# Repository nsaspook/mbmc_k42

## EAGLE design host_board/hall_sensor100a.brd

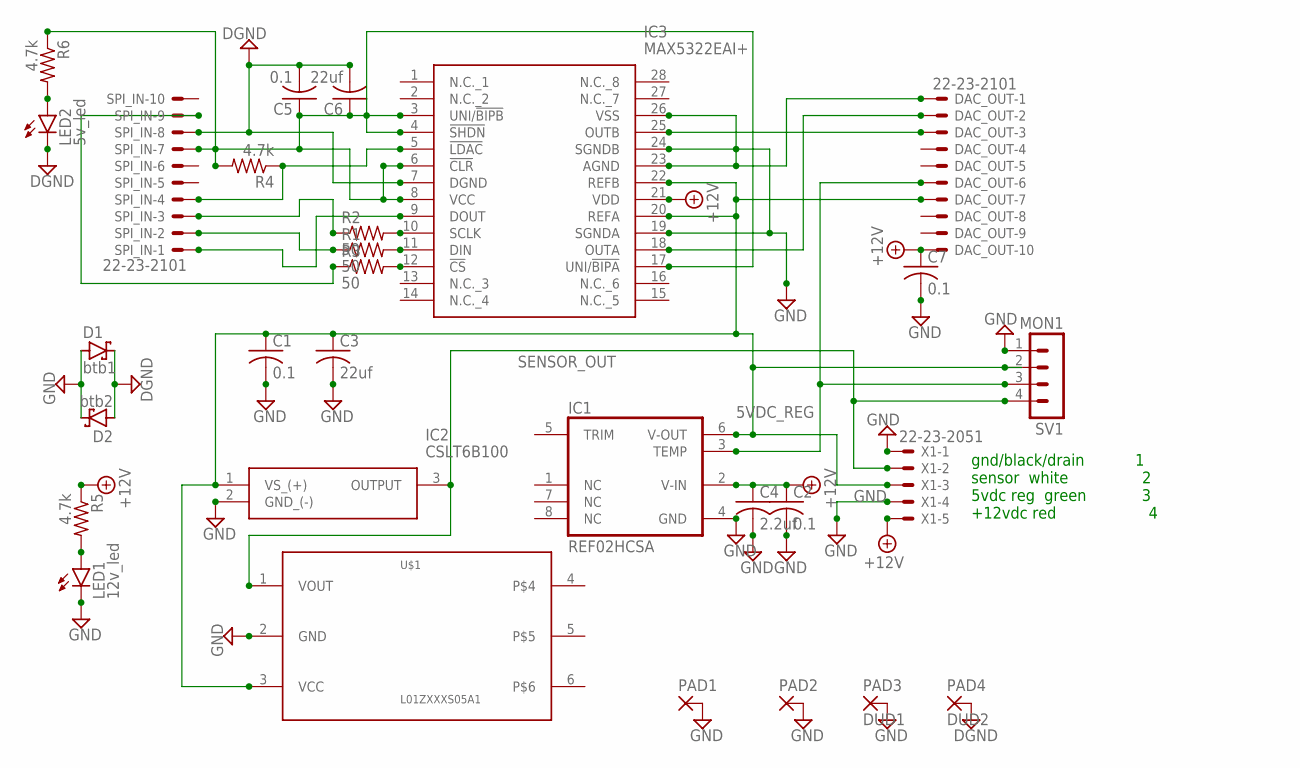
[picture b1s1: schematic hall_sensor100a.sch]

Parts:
C1, C2, C5, C7: 0.1; C0805
C3, C6: 22uf; C0805
C4: 2.2uf; C0805
D1: btb1; DO35-7
D2: btb2; DO35-7
DAC_OUT: 22-23-2101
IC1: REF02HCSA; SO08
IC2: CSLT6B100
IC3: MAX5322EAI+; SOP65P778X199-28N
LED1: 12v_led; CHIPLED_1206
LED2: 5v_led; CHIPLED_1206
PAD1, PAD2: 2,15/1,0
PAD3: DUD1; 2,15/1,0
PAD4: DUD2; 2,15/1,0
R1, R2, R3: 50; M0805
R4, R5, R6: 4.7k; M0805
SPI_IN: 22-23-2101
SV1: MON1; MA04-1
U$1: L01ZXXXS05A1; DIP2540W53P254L2900H508Q6B
X1: 22-23-2051

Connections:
5VDC_REG: C1.1, C3.1, DAC_OUT.7, IC1.6 (V-OUT), IC2.1 (VS_(+)), IC3.20 (REFA), IC3.22 (REFB), SV1.2, U$1.3 (VCC), X1.3
+12V: C2.1, C4.1, C7.1, DAC_OUT.10, IC1.2 (V-IN), IC3.21 (VDD), R5.1, X1.5
DGND: C5.2, C6.2, D1.C, D2.A, IC3.7 (DGND), LED2.C, PAD4.1, SPI_IN.8
GND: C1.2, C2.2, C3.2, C4.2, C7.2, D1.A, D2.C, DAC_OUT.1, IC1.4 (GND), IC2.2 (GND_(-)), IC3.19 (SGNDA), IC3.23 (AGND), IC3.24 (SGNDB), IC3.26 (VSS), LED1.C, PAD1.1, PAD2.1, PAD3.1, SV1.1, U$1.2 (GND), X1.1, X1.4
unnamed: IC3.11 (DIN), R1.2
unnamed: DAC_OUT.2, IC3.18 (OUTA)
unnamed: DAC_OUT.3, IC3.25 (OUTB)
unnamed: R1.1, SPI_IN.2
unnamed: IC3.9 (DOUT), SPI_IN.1
unnamed: R2.1, SPI_IN.3
unnamed: R3.1, SPI_IN.9
unnamed: C5.1, C6.1, IC3.3 (UNI/!BIPB), IC3.4 (!SHDN), IC3.6 (!CLR), IC3.8 (VCC), IC3.17 (UNI/!BIPA), R4.2, R6.1, SPI_IN.7
unnamed: LED1.A, R5.2
unnamed: IC3.5 (!LDAC), R4.1, SPI_IN.4
unnamed: IC3.10 (SCLK), R2.2
unnamed: IC3.12 (!CS), R3.2
unnamed: DAC_OUT.6, IC1.3 (TEMP), SV1.3
unnamed: LED2.A, R6.2
SENSOR_OUT: IC2.3 (OUTPUT), SV1.4, U$1.1 (VOUT), X1.2

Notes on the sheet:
gnd/black/drain 1 sensor white 2 5vdc reg green 3 +12vdc red 4

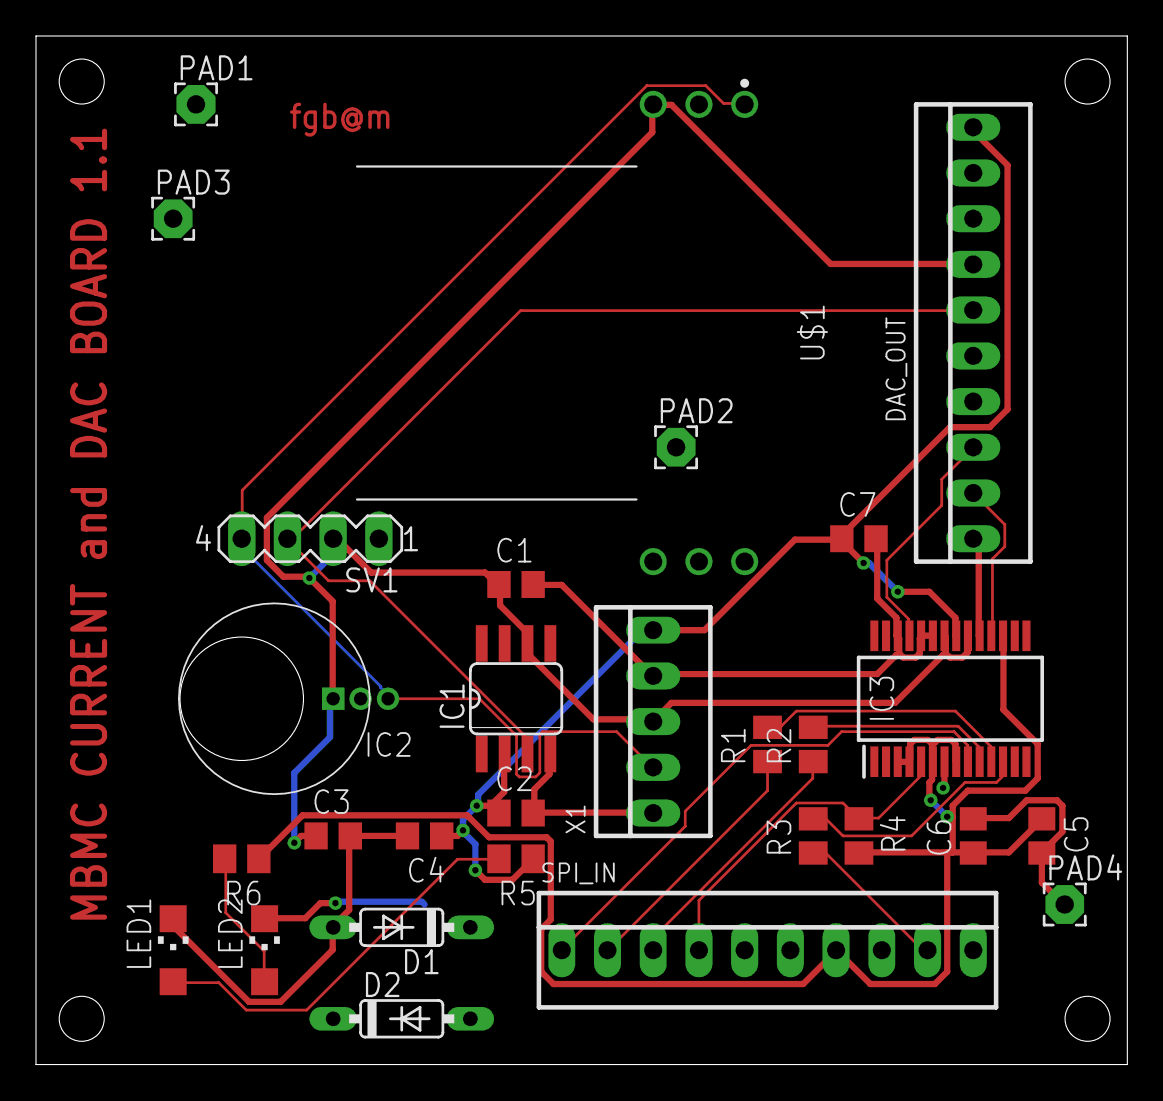
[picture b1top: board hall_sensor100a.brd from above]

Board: 2 copper layers, 60.6 x 57.1 mm, 29 parts (0 on the bottom side), 19 nets.

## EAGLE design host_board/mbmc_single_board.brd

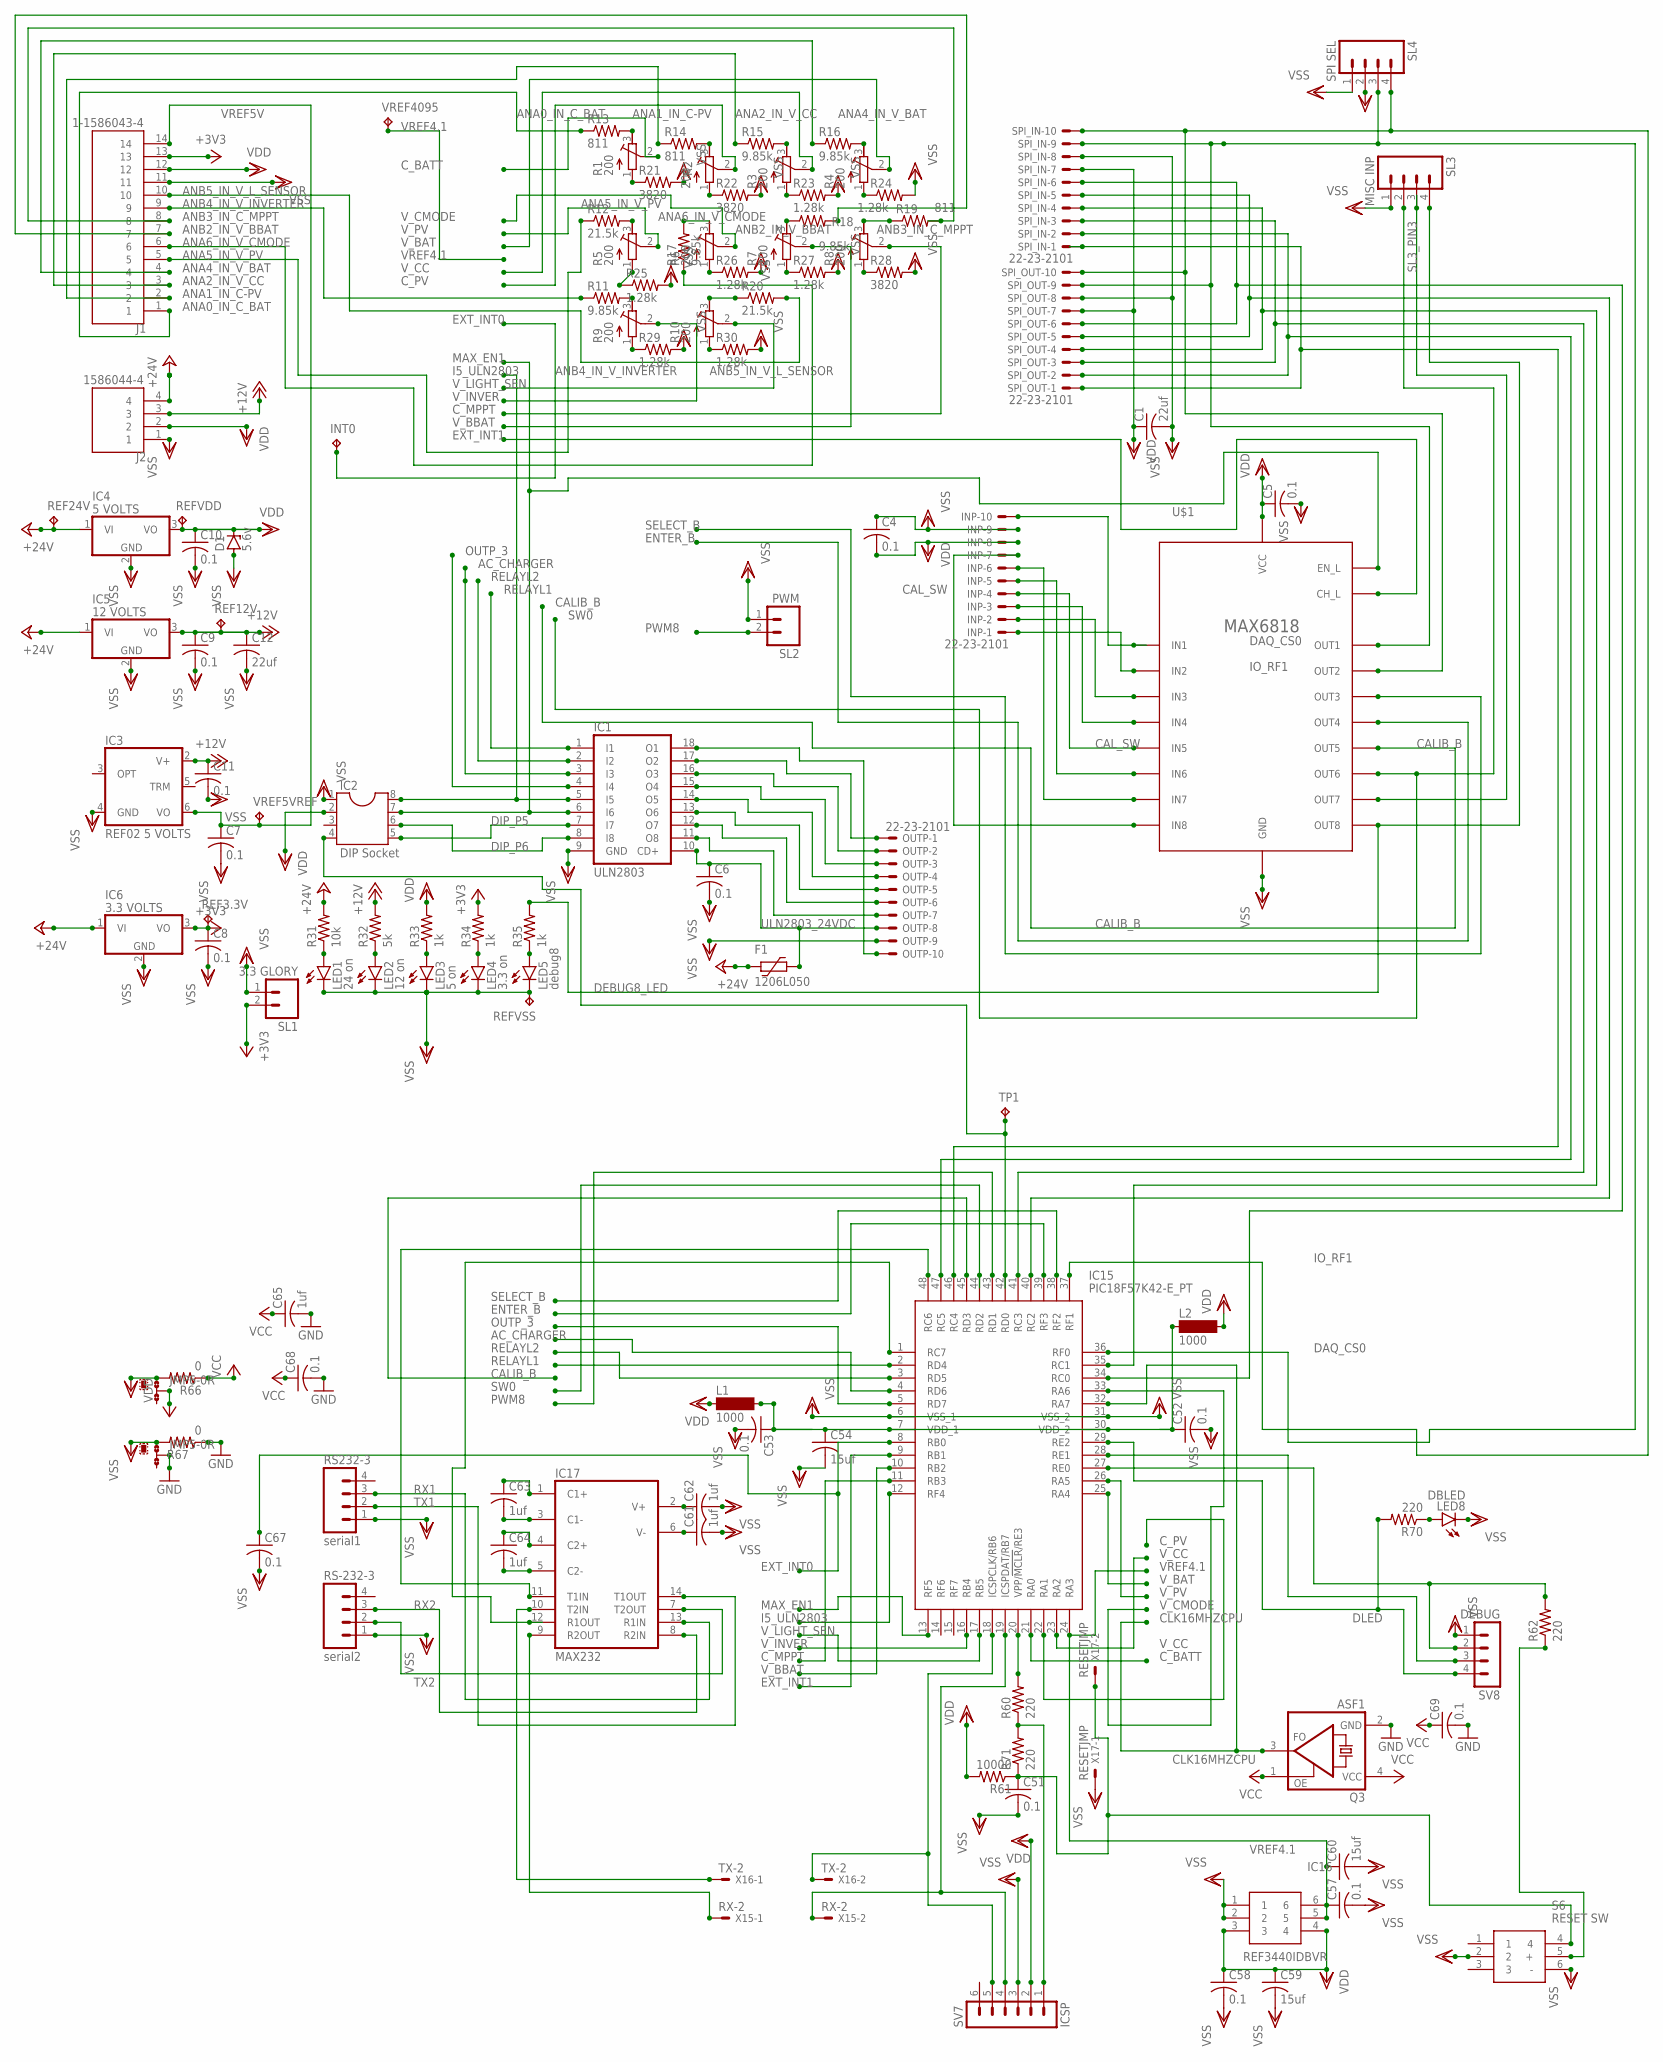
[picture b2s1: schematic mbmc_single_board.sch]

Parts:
C1, C12: 22uf; C0805
C4, C5, C6, C7, C8, C9, C10, C11: 0.1; C0805
C51, C52, C53, C57, C58, C67, C68, C69: 0.1; C1206
C54, C59, C60: 15uf; C1206
C61, C62, C63, C64, C65: 1uf; C0805
D1: 5.6v; ZDIO-2.5
F1: 1206L050; 1206L
IC1: ULN2803; DIL18
IC2: DIP Socket; SOCKET-08
IC3: REF02 5 VOLTS; DIL08
IC4: 5 VOLTS; TO220V
IC5: 12 VOLTS; TO220V
IC6: 3.3 VOLTS; TO220V
IC15: PIC18F57K42-E_PT; QFP50P900X900X120-48N
IC16: REF3440IDBVR; SOP95P280X145-6N
IC17: MAX232; DIL16
INP: 22-23-2101
INT0: TPB1,27; B1,27
J1: 1-1586043-4; TE_1-1586043-4
J2: 1586044-4; TE_1586044-4
JMP5, JMP6: 0R-JUMPA; A0R-JMP
L1, L2: 1000; SM-1206
LED1: 24 on; CHIPLED_1206
LED2: 12 on; CHIPLED_1206
LED3: 5 on; CHIPLED_1206
LED4: 3.3 on; CHIPLED_1206
LED5: debug8; CHIPLED_1206
LED8: DBLED; CHIPLED_1206
OUTP: 22-23-2101
Q3: ASF1; ASF
R1, R2, R3, R4, R5, R6, R7, R8, R9, R10: 200; RTRIM3339P
R11, R15, R16, R17, R18: 9.85k; R0805
R12, R20: 21.5k; R0805
R13, R14, R19: 811; R0805
R21, R22, R28: 3820; R0805
R23, R24, R25, R26, R27, R29, R30: 1.28k; R0805
R31: 10k; R0805
R32: 5k; R0805
R33, R34, R35: 1k; R0805
R60, R62, R70, R71: 220; R1206
R61: 10000; R1206
R66, R67: 0; R1206
REF3.3V, REF12V, REF24V: TPB1,27; B1,27
REFVDD: TPB1,27; B1,27
REFVSS: TPB1,27; B1,27
RS232-3: serial1; 04P
RS-232-3: serial2; 04P
S6: RESET SW; B3W-9_1-LED
SL1: 3.3 GLORY; 02P
SL2: PWM; 02P
SL3: MISC INP; 04P
SL4: SPI SEL; 04P
SPI_IN: 22-23-2101
SPI_OUT: 22-23-2101
SV7: ICSP; MA06-1
SV8: DEBUG; MA04-1
TP1: TPB1,27; B1,27
U$1: MAX6818; SSOP20
VREF5VREF, VREF4095: TPB1,27; B1,27
X15: RX-2; 332-02
X16: TX-2; 332-02
X17: RESETJMP; 332-02

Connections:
+3V3: C8.1, IC6.3 (VO), J1.13, R34.2, REF3.3V.TP, SL1.2
+12V: C9.1, C11.1, C12.1, IC3.2 (V+), IC5.3 (VO), J2.3, R32.2, REF12V.TP
+24V: F1.2, IC4.1 (VI), IC5.1 (VI), IC6.1 (VI), J2.4, R31.2, REF24V.TP
AC_CHARGER: IC1.3 (I3), IC15.4 (RD6)
ANA0_IN_C_BAT: J1.1, R13.1
ANA1_IN_C-PV: J1.2, R14.1
ANA2_IN_V_CC: J1.3, R15.1
ANA4_IN_V_BAT: J1.4, R16.1
ANA5_IN_V_PV: J1.5, R12.1
ANA6_IN_V_CMODE: J1.6, R17.1
ANB2_IN_V_BBAT: J1.7, R18.2
ANB3_IN_C_MPPT: J1.8, R19.2
ANB4_IN_V_INVERTER: J1.9, R11.1
ANB5_IN_V_L_SENSOR: J1.10, R20.2
CALIB_B: IC15.45 (RD3), U$1.OUT5
CAL_SW: INP.4, U$1.IN5
CLK16MHZCPU: IC15.32 (RA7), Q3.3 (FO)
C_BATT: IC15.21 (RA0), R1.2 (S)
C_MPPT: IC15.11 (RB3), R8.2 (S)
C_PV: IC15.22 (RA1), R2.2 (S)
DAQ_CS0: IC15.36 (RF0), SL4.3, SPI_IN.9, SPI_OUT.9, U$1.OUT1
DEBUG8_LED: R35.2, SL3.4, U$1.OUT8
DIP_P5: IC1.7 (I7), IC2.5
DIP_P6: IC1.8 (I8), IC2.6
DLED: IC15.29 (RE2), R70.2, SV8.4
ENTER_B: IC15.39 (RF3), U$1.OUT4
EXT_INT0: C67.1, IC15.8 (RB0), INT0.TP
EXT_INT1: IC15.9 (RB1), U$1.CH_L
GND: C65.2, C68.2, C69.2, IC17.15 (GND), JMP5.2, Q3.2 (GND), R67.1
I5_ULN2803: IC1.5 (I5), IC2.8, IC15.12 (RF4)
IO_RF1: IC15.37 (RF1), SL4.4, SPI_IN.10, SPI_OUT.10, U$1.OUT2
MAX_EN1: IC1.6 (I6), IC2.7, IC15.13 (RF5), U$1.EN_L
unnamed: R9.3 (E), R11.2
unnamed: R5.3 (E), R12.2
unnamed: R1.3 (E), R13.2
unnamed: R2.3 (E), R14.2
unnamed: R3.3 (E), R15.2
unnamed: R4.3 (E), R16.2
unnamed: R6.3 (E), R17.2
unnamed: R8.3 (E), R19.1
unnamed: R1.1 (A), R21.1
unnamed: R2.1 (A), R22.1
unnamed: R3.1 (A), R23.1
unnamed: R4.1 (A), R24.1
unnamed: R5.1 (A), R25.1
unnamed: R6.1 (A), R26.1
unnamed: R7.1 (A), R27.1
unnamed: R8.1 (A), R28.1
unnamed: R9.1 (A), R29.1
unnamed: R10.1 (A), R30.1
unnamed: C52.1, C53.1, C54.1, IC15.7 (VDD_1), IC15.30 (VDD_2), L1.2, L2.1
unnamed: INP.10, U$1.IN1
unnamed: INP.1, U$1.IN2
unnamed: INP.2, U$1.IN3
unnamed: INP.3, U$1.IN4
unnamed: INP.5, U$1.IN6
unnamed: INP.6, U$1.IN7
unnamed: INP.7, U$1.IN8
unnamed: IC1.18 (O1), OUTP.10
unnamed: IC1.17 (O2), OUTP.1
unnamed: IC1.16 (O3), OUTP.2
unnamed: IC1.15 (O4), OUTP.3
unnamed: IC1.14 (O5), OUTP.4
unnamed: IC1.13 (O6), OUTP.5
unnamed: IC1.12 (O7), OUTP.6
unnamed: IC1.11 (O8), OUTP.7
unnamed: IC15.46 (RC4), SPI_IN.1, SPI_OUT.1
unnamed: LED1.A, R31.1
unnamed: LED2.A, R32.1
unnamed: LED3.A, R33.1
unnamed: LED4.A, R34.1
unnamed: LED5.A, R35.1
unnamed: R10.3 (E), R20.1
unnamed: R7.3 (E), R18.1
unnamed: IC15.20 (VPP/!MCLR!/RE3), R60.2
unnamed: IC15.19 (ICSPDAT/RB7), SV7.4, X15.2
unnamed: IC15.18 (ICSPCLK/RB6), SV7.5, X16.2
unnamed: C61.1, IC17.6 (V-)
unnamed: C62.1, IC17.2 (V+)
unnamed: C63.1, IC17.1 (C1+)
unnamed: C64.1, IC17.4 (C2+)
unnamed: C64.2, IC17.5 (C2-)
unnamed: C63.2, IC17.3 (C1-)
unnamed: IC15.1 (RC7), IC17.12 (R1OUT)
unnamed: IC17.9 (R2OUT), X15.1
unnamed: IC15.48 (RC6), IC17.11 (T1IN)
unnamed: IC17.10 (T2IN), X16.1
unnamed: R62.1, S6.5 (+)
unnamed: IC15.27 (RE0), R62.2, SV8.2
unnamed: IC15.28 (RE1), SV8.3
unnamed: IC2.4, IC15.42 (RD0), TP1.TP
unnamed: IC15.47 (RC5), SPI_IN.2, SPI_OUT.2
unnamed: IC15.41 (RC3), SPI_IN.3, SPI_OUT.3
unnamed: IC15.35 (RC1), SPI_IN.4, SPI_OUT.4
unnamed: IC15.40 (RC2), SPI_IN.5, SPI_OUT.5
unnamed: IC15.34 (RC0), SPI_IN.6, SPI_OUT.6
unnamed: LED8.A, R70.1
unnamed: C51.1, R61.1, R71.1, S6.4, X17.2
unnamed: R60.1, R71.2, SV7.1
OUTP_3: IC1.4 (I4), IC15.5 (RD7)
PWM8: IC15.43 (RD1), SL2.2
RELAYL1: IC1.1 (I1), IC15.2 (RD4)
RELAYL2: IC1.2 (I2), IC15.3 (RD5)
RX1: IC17.13 (R1IN), RS232-3.3
RX2: IC17.8 (R2IN), RS-232-3.3
SELECT_B: IC15.38 (RF2), U$1.OUT3
SL3_PIN3: SL3.3, U$1.OUT7
SW0: IC15.44 (RD2), SL3.2, U$1.OUT6
TX1: IC17.14 (T1OUT), RS232-3.2
TX2: IC17.7 (T2OUT), RS-232-3.2
ULN2803_24VDC: C6.1, F1.1, IC1.10 (CD+), OUTP.8
VCC: C65.1, C68.1, C69.1, IC17.16 (VCC), JMP6.2, Q3.1 (OE), Q3.4 (VCC), R66.1
VDD: C1.1, C4.2, C5.1, C10.1, C58.1, C59.1, D1.C, IC2.2, IC4.3 (VO), IC16.3, IC16.4, INP.8, J1.12, J2.2, JMP6.1, L1.1, L2.2, R33.2, R61.2, R66.2, REFVDD.TP, SL4.2, SPI_IN.7, SPI_OUT.7, SV7.2, U$1.VCC
VREF4.1: C57.1, C60.1, IC15.24 (RA3), IC16.5, IC16.6, VREF4095.TP
VREF5V: C7.1, IC3.6 (VO), J1.14, VREF5VREF.TP
VSS: C1.2, C4.1, C5.2, C6.2, C7.2, C8.2, C9.2, C10.2, C11.2, C12.2, C51.2, C52.2, C53.2, C54.2, C57.2, C58.2, C59.2, C60.2, C61.2, C62.2, C67.2, D1.A, IC1.9 (GND), IC2.1, IC3.4 (GND), IC4.2 (GND), IC5.2 (GND), IC6.2 (GND), IC15.6 (VSS_1), IC15.31 (VSS_2), IC16.1, IC16.2, INP.9, J1.11, J2.1, JMP5.1, LED1.C, LED2.C, LED3.C, LED4.C, LED5.C, LED8.C, OUTP.9, R21.2, R22.2, R23.2, R24.2, R25.2, R26.2, R27.2, R28.2, R29.2, R30.2, R67.2, REFVSS.TP, RS232-3.1, RS-232-3.1, S6.2, S6.6 (-), SL1.1, SL2.1, SL3.1, SL4.1, SPI_IN.8, SPI_OUT.8, SV7.3, SV8.1, U$1.GND, X17.1
V_BAT: IC15.25 (RA4), R4.2 (S)
V_BBAT: IC15.10 (RB2), R7.2 (S)
V_CC: IC15.23 (RA2), R3.2 (S)
V_CMODE: IC15.33 (RA6), R6.2 (S)
V_INVER: IC15.16 (RB4), R9.2 (S)
V_LIGHT_SEN: IC15.17 (RB5), R10.2 (S)
V_PV: IC15.26 (RA5), R5.2 (S)

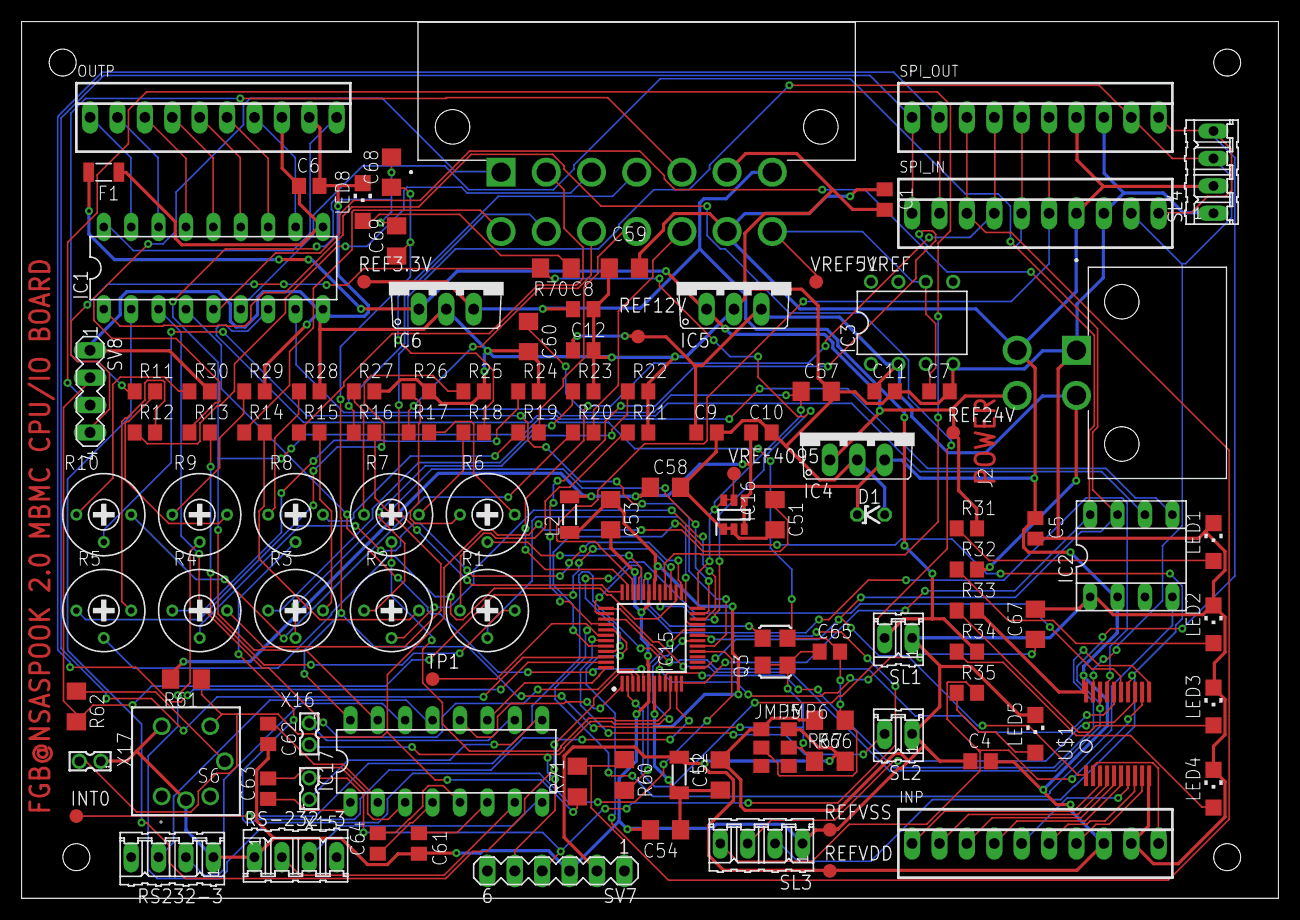
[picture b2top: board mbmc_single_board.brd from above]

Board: 2 copper layers, 116.5 x 81.3 mm, 118 parts (0 on the bottom side), 123 nets.

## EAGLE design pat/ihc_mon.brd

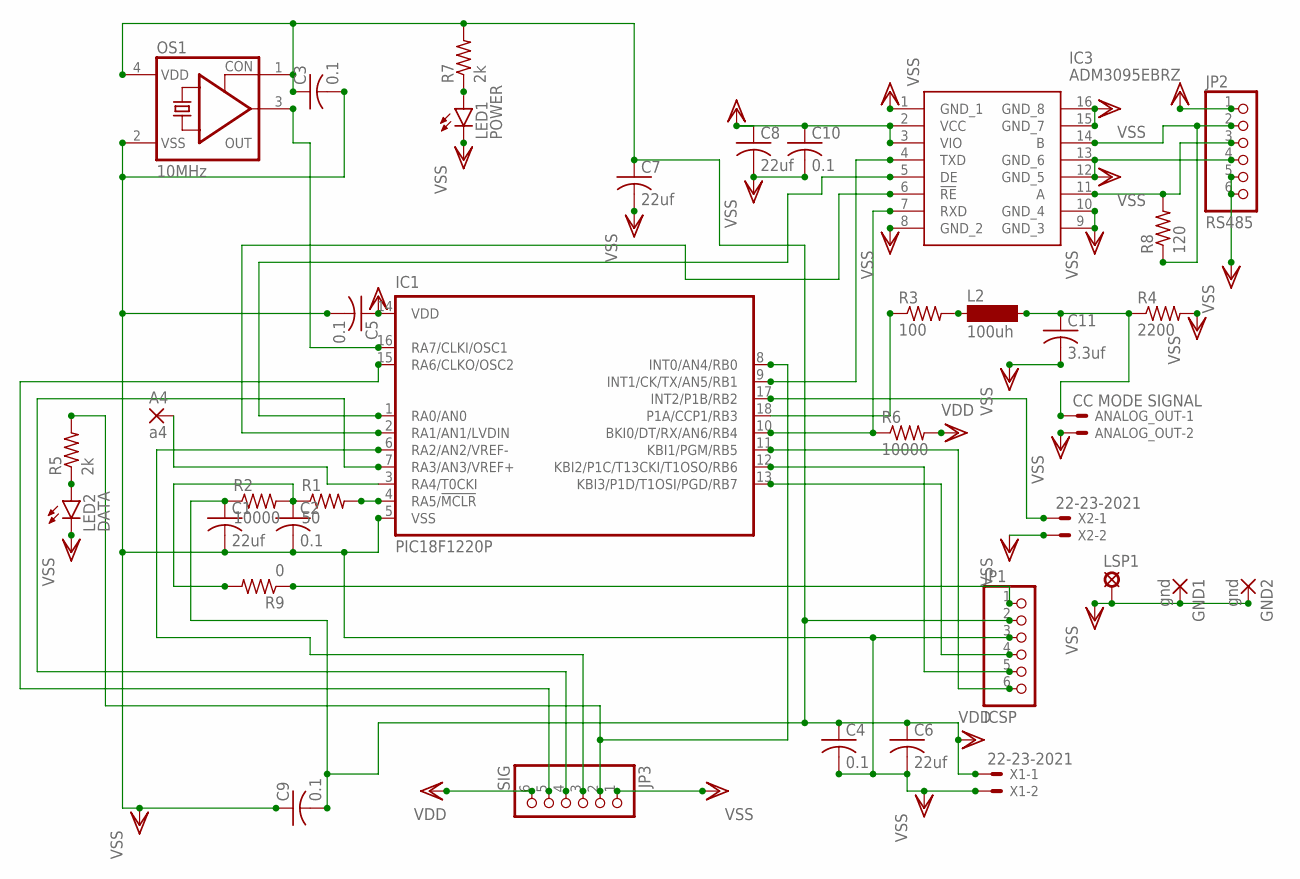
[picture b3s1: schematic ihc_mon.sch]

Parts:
A4: a4; SMD1,27-2,54
ANALOG_OUT: CC MODE SIGNAL; 22-23-2021
C1, C6, C7, C8: 22uf; C0805
C2, C3, C4, C5, C9, C10: 0.1; C0805
C11: 3.3uf; C0805
GND1: gnd; 3,81/1,4
GND2: gnd; SMD1,27-2,54
IC1: PIC18F1220P; DIL18; MPN PIC18F1320-I/P
IC3: ADM3095EBRZ; SOIC127P600X175-16N
JP1: ICSP; 1X06
JP2: RS485; 1X06
JP3: SIG; 1X06
L2: 100uh; SM-1206
LED1: POWER; CHIPLED_1206
LED2: DATA; CHIPLED_1206
LSP1: SE14
OS1: 10MHz; 7.2X5.2-4-PAD
R1: 50; R0805
R2, R6: 10000; R0805
R3: 100; R0805
R4: 2200; R0805
R5, R7: 2k; R0805
R8: 120; M1206
R9: 0; R0805
X1, X2: 22-23-2021

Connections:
unnamed: IC1.10 (BKI0/DT/RX/AN6/RB4), IC3.7 (RXD), R6.1
unnamed: IC1.9 (INT1/CK/TX/AN5/RB1), IC3.4 (TXD)
unnamed: IC1.1 (RA0/AN0), IC3.5 (DE)
unnamed: IC1.2 (RA1/AN1/LVDIN), IC3.6 (!RE)
unnamed: IC1.4 (RA5/!MCLR), R1.2
unnamed: IC1.18 (P1A/CCP1/RB3), R3.1
unnamed: L2.1, R3.2
unnamed: IC3.14 (B), JP2.2, R8.1
unnamed: IC3.11 (A), JP2.3, R8.2
unnamed: IC1.17 (INT2/P1B/RB2), X2.1
unnamed: ANALOG_OUT.1, C11.1, L2.2, R4.1
unnamed: JP1.1, R9.1
unnamed: LED2.A, R5.1
unnamed: LED1.A, R7.1
unnamed: IC1.11 (KBI1/PGM/RB5), JP1.6
unnamed: A4.1, IC1.3 (RA4/T0CKI)
unnamed: IC1.8 (INT0/AN4/RB0), JP3.2, R5.2
unnamed: IC1.6 (RA2/AN2/VREF-), JP3.3
unnamed: IC1.12 (KBI2/P1C/T13CKI/T1OSO/RB6), JP1.5
unnamed: IC1.13 (KBI3/P1D/T1OSI/PGD/RB7), JP1.4
unnamed: C2.1, R1.1, R2.2, R9.2
unnamed: IC1.16 (RA7/CLKI/OSC1), OS1.3 (OUT)
SIG4: IC1.7 (RA3/AN3/VREF+), JP3.4
SIG5: IC1.15 (RA6/CLKO/OSC2), JP3.5
VDD: C1.1, C3.1, C4.1, C5.1, C6.1, C7.1, C8.1, C9.2, C10.1, IC1.14 (VDD), IC3.2 (VCC), IC3.3 (VIO), JP1.2, JP2.1, JP3.6, OS1.1 (CON), OS1.4 (VDD), R2.1, R6.2, R7.2, X1.1
VSS: ANALOG_OUT.2, C1.2, C2.2, C3.2, C4.2, C5.2, C6.2, C7.2, C8.2, C9.1, C10.2, C11.2, GND1.1, GND2.1, IC1.5 (VSS), IC3.1 (GND_1), IC3.8 (GND_2), IC3.9 (GND_3), IC3.10 (GND_4), IC3.12 (GND_5), IC3.13 (GND_6), IC3.15 (GND_7), IC3.16 (GND_8), JP1.3, JP2.4, JP2.5, JP2.6, JP3.1, LED1.C, LED2.C, LSP1.MP, OS1.2 (VSS), R4.2, X1.2, X2.2

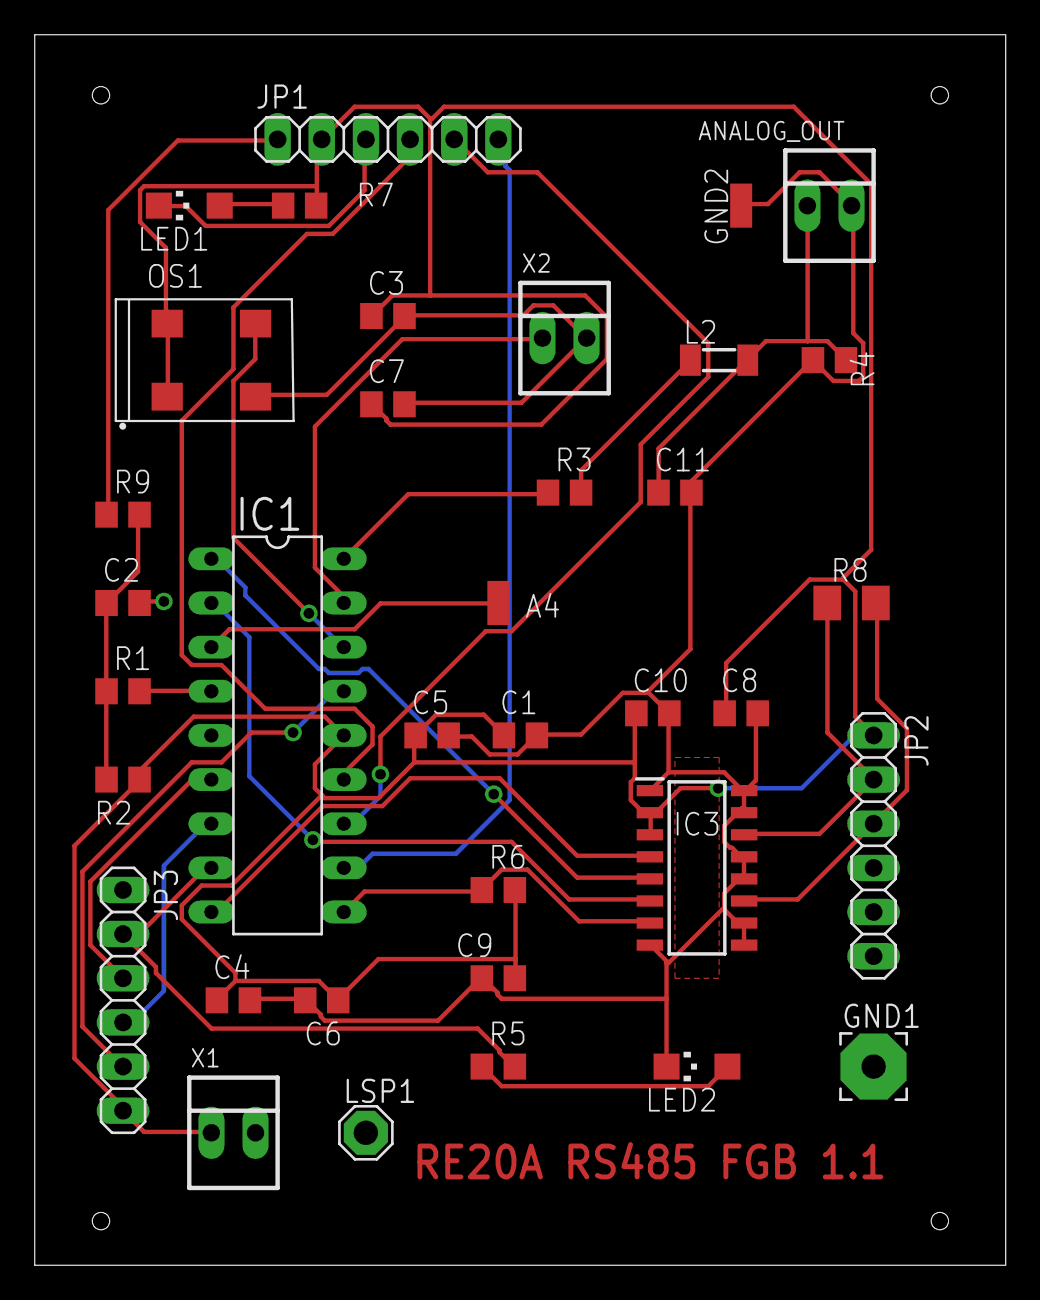
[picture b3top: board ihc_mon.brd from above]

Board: 2 copper layers, 55.9 x 70.8 mm, 36 parts (0 on the bottom side), 26 nets.

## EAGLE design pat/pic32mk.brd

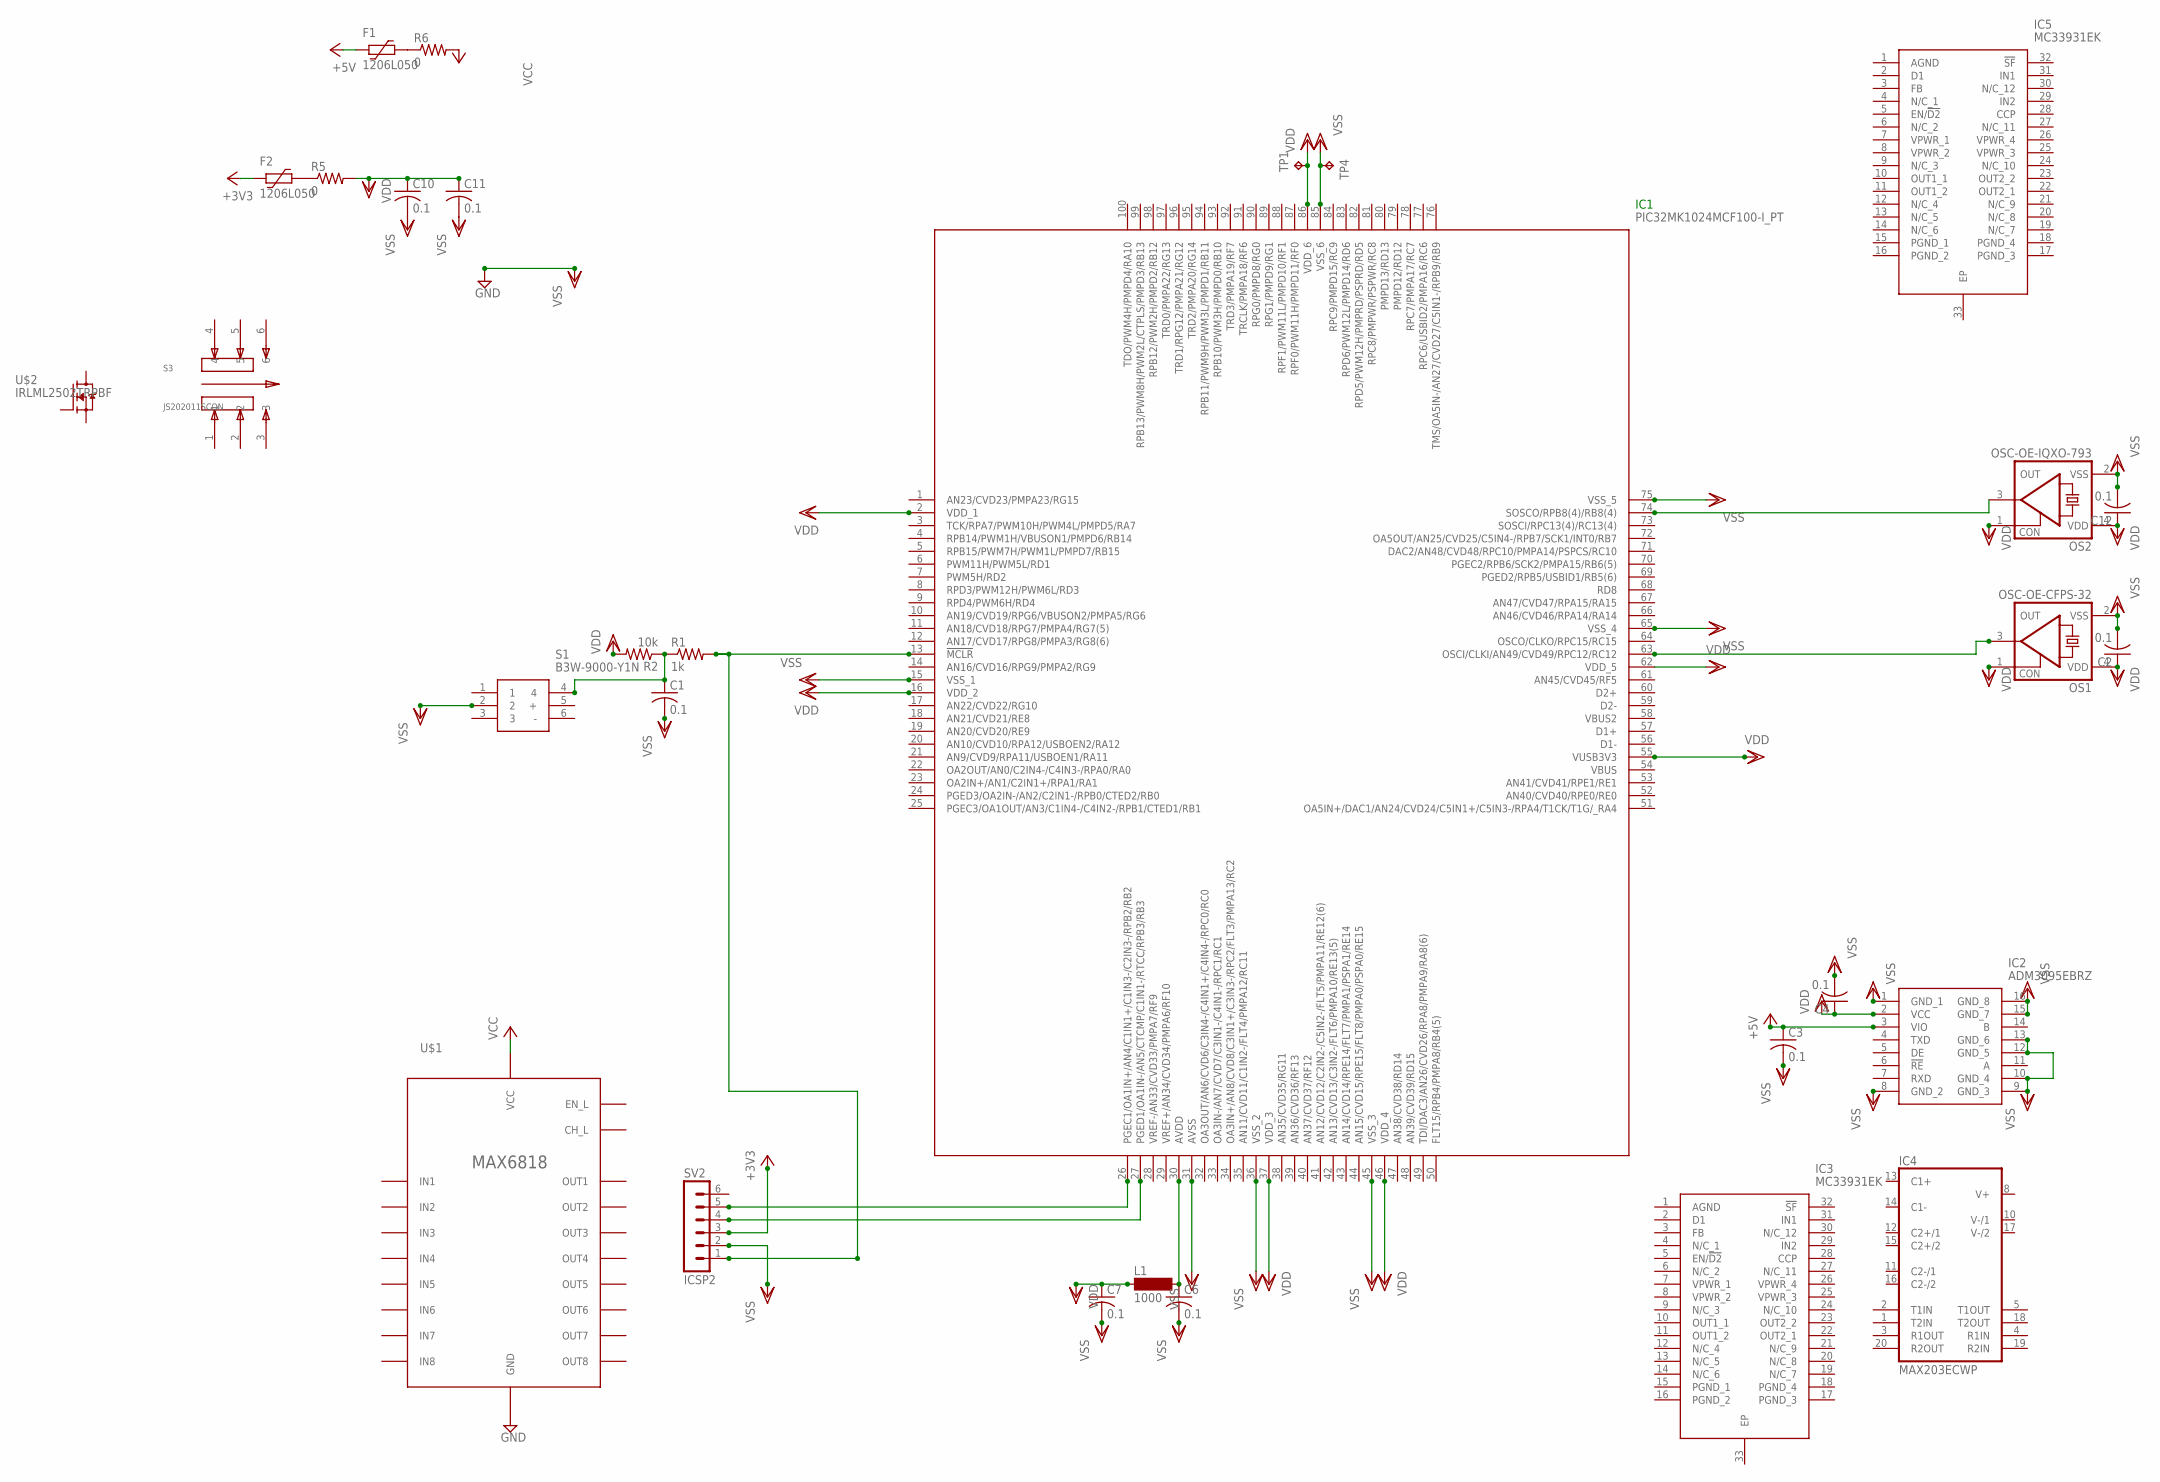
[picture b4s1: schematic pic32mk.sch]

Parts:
C1, C2, C3, C4, C6, C7, C10, C11, C12: 0.1; C0805
F1, F2: 1206L050; 1206L
IC1: PIC32MK1024MCF100-I_PT; QFP40P1400X1400X120-100N
IC2: ADM3095EBRZ; SOIC127P600X175-16N
IC3, IC5: MC33931EK; SOP65P1030X245-33N
IC4: MAX203ECWP; SO20L
L1: 1000; SM-1206
OS1: OSC-OE-CFPS-32; 7.2X5.2-4-PAD
OS2: OSC-OE-IQXO-793; 2.5X2-4-PAD
R1: 1k; M0805
R2: 10k; M0805
R5, R6: 0; M0805
S1: B3W-9000-Y1N; B3W-9_1-LED
S3: JS202011SCQN; SW_JS202011SCQN
SV2: ICSP2; MA06-1
TP1, TP4: TPB1,27; B1,27
U$1: MAX6818; SSOP20
U$2: IRLML2502TRPBF; SOT23

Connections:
+3V3: F2.2, SV2.3
+5V: C3.1, F1.2, IC2.3 (VIO)
GND: IC4.6 (GND), IC4.9 (GND), U$1.GND
unnamed: C1.1, R1.1, R2.1, S1.4
unnamed: IC1.13 (!MCLR), R1.2, SV2.1
unnamed: F2.1, R5.1
unnamed: C6.1, IC1.30 (AVDD), L1.2
unnamed: IC1.63 (OSCI/CLKI/AN49/CVD49/RPC12/RC12), OS1.3 (OUT)
unnamed: F1.1, R6.1
unnamed: IC1.27 (PGED1/OA1IN-/AN5/CTCMP/C1IN1-/RTCC/RPB3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), SV2.4
unnamed: IC1.26 (PGEC1/OA1IN+/AN4/C1IN1+/C1IN3-/C2IN3-/R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), SV2.5
unnamed: IC1.74 (SOSCO/RPB8(4)/RB8(4)), OS2.3 (OUT)
VCC: IC4.7 (VCC), R6.2, U$1.VCC
VDD: C2.1, C4.1, C7.1, C10.1, C11.1, C12.1, IC1.2 (VDD_1), IC1.16 (VDD_2), IC1.37 (VDD_3), IC1.46 (VDD_4), IC1.55 (VUSB3V3), IC1.62 (VDD_5), IC1.86 (VDD_6), IC2.2 (VCC), L1.1, OS1.1 (CON), OS1.4 (VDD), OS2.1 (CON), OS2.4 (VDD), R2.2, R5.2, TP1.TP
VSS: C1.2, C2.2, C3.2, C4.2, C6.2, C7.2, C10.2, C11.2, C12.2, IC1.15 (VSS_1), IC1.31 (AVSS), IC1.36 (VSS_2), IC1.45 (VSS_3), IC1.65 (VSS_4), IC1.75 (VSS_5), IC1.85 (VSS_6), IC2.1 (GND_1), IC2.8 (GND_2), IC2.9 (GND_3), IC2.10 (GND_4), IC2.12 (GND_5), IC2.13 (GND_6), IC2.15 (GND_7), IC2.16 (GND_8), OS1.2 (VSS), OS2.2 (VSS), S1.2, SV2.2, TP4.TP

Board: 2 copper layers, 30 parts (0 on the bottom side), 15 nets, no tracks yet.

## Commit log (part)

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2020-11-29 new git for MBMC for 24 volt systems
2024-01-30 alpha version 2.10
2024-10-19 correct AH calcs
2025-03-19 clean up files for doxygen docs
2025-08-19 checkpoint
